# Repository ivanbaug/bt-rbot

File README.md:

# Bluetooth robot
It's a bluetooth controlled robot using arduino for a microcontroller and android phone as a remote.

## Mechanical parts
The pieces were laser cutted in 4mm MDF, the files for the cut are in the `parts/` folder.

## Electronics
It's a handmade board containing an arduino pro-mini, an hc06 bluetooth module and an lm293d to drive the wheel motors. (Check the `images/` folder for better resolution).

There is also a cheap DC-DC converter from aliexpress to stepdown the battery from 9v to 5v. Arms are driven by two servomotors that feed directly from the 5v source.

## Code
There are two parts to this: an arduino file that controls the physical robot.

Then there's an android studio project, made in Java. Beware that this project targets a specific android version (view `app\build.gradle` file) since it was meant to be gifted to a kid in my family that uses a somewhat outdated android phone.

### Video

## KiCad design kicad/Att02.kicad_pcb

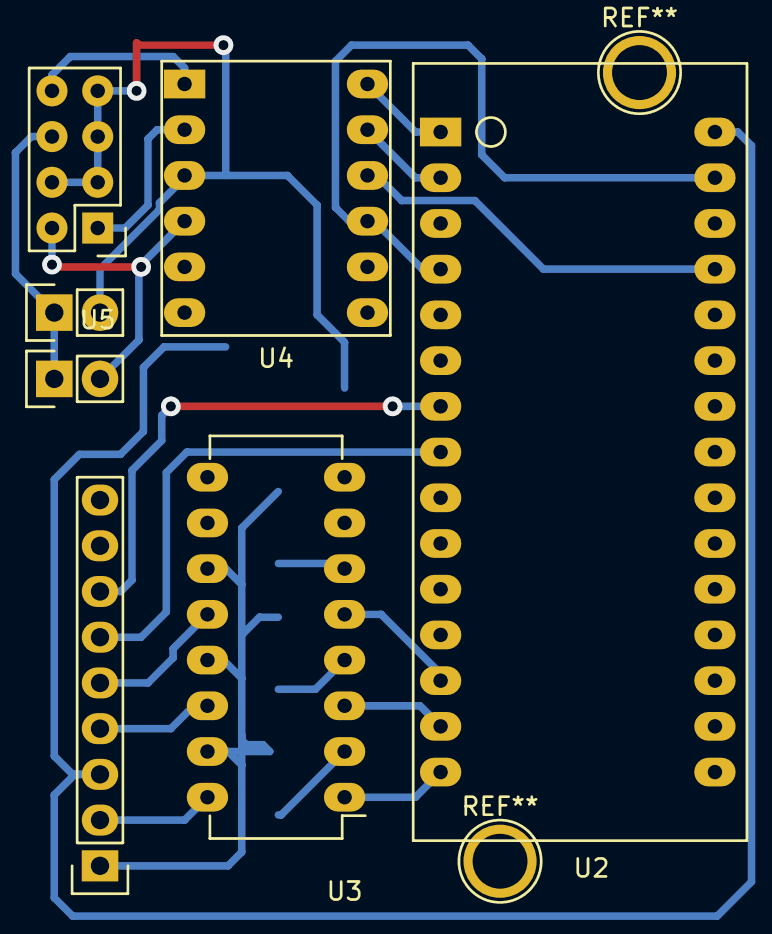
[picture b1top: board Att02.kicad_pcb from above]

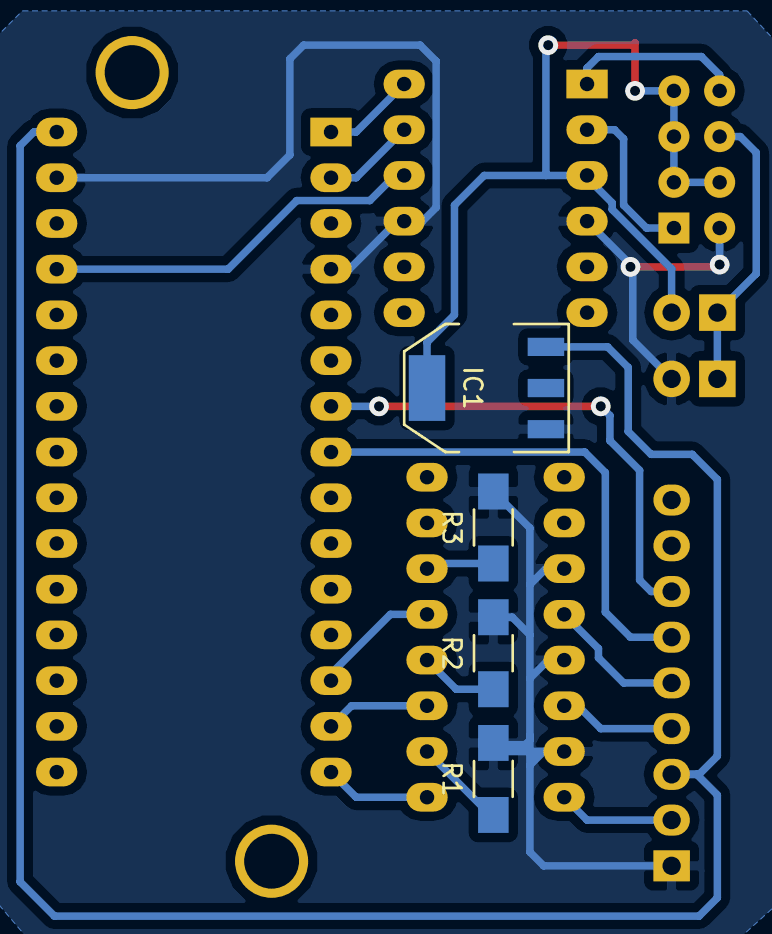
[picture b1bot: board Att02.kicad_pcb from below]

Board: 2 copper layers, 11 parts (4 on the bottom side), 20 nets.

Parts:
IC1: LM1117; SOT-223
P1, P2: CONN_01X02; Pin_Header_Straight_1x02
R1, R2, R3: R; R_1206_HandSoldering
U1: Connector_FM_Iv; Pin_Header_Straight_1x09
U2: ArduinoNano; ard_nano_2x15
U3: PS2501a-4; DIP-16_W7.62mm_LongPads
U4: 5VTO3V3; level_converter
U5: ESP8266; Pin_Header_Straight_2x04

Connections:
3.3v: IC1.2, IC1.4, P2.2, U4.3, U5.3, U5.4, U5.5, U5.7
5v: U2.27, U4.10
+6V: IC1.3, U1.3, U2.30
CD_H: U1.5, U3.12
CD_L: U2.13, U3.5
GND: IC1.1, P1.2, R1.2, R2.2, R3.2, U1.1, U2.4, U2.29, U3.11, U3.13, U3.15, U4.4, U4.9, U5.2
GPIO_0: P1.1, P2.1, U5.6
M1: U1.6, U2.8
M2: U1.7, U2.7
unnamed: R1.1, U3.2
unnamed: R2.1, U3.4
unnamed: R3.1, U3.6
ON_OFF_H: U1.2, U3.16
ON_OFF_L: U2.15, U3.1
RX_H: U2.2, U4.11
RX_L: U4.1, U5.8
TUNER_H: U1.4, U3.14
TUNER_L: U2.14, U3.3
TX_H: U2.1, U4.12
TX_L: U4.2, U5.1

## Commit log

2021-08-15 Add code for arduino board
2021-08-16 Commit android studio project for backup purposes
    I made this project some time ago without version control
    Now this commit is pretty much the entire project, next commit is probably a readme.
2021-08-17 add drawing of mechanical parts
2021-08-17 add the kicad electronic project files
2021-08-17 add readme
2021-08-17 ammend
2021-08-18 remove unnecesary folder
2021-08-18 add images and update readme
2021-08-18 mend
